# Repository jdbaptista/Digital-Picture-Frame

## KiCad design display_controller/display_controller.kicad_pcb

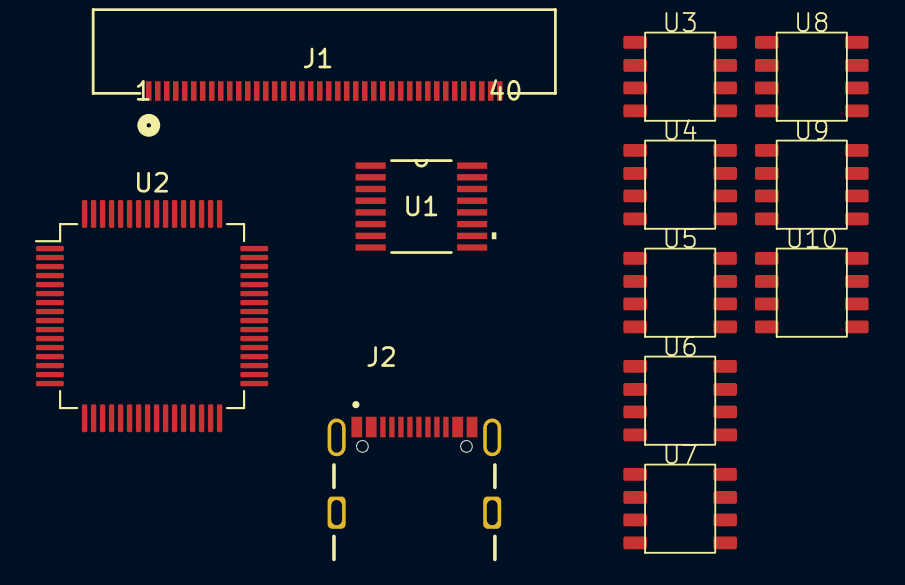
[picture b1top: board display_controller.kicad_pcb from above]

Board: 2 copper layers, 12 parts (0 on the bottom side), 10 nets, no tracks yet.

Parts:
J1: FPC CONN; CONN_4-1734592-0_TYCO
J2: USB4105GFA120; GCT_USB4105GFA120
U1: LVDS391; PW16
U2: STM32F412RETx; LQFP-64_10x10mm_P0.5mm
U3, U4, U5, U6, U7, U8, U9, U10: GD25Q16; SOP8 150mil

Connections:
GND: J1.7 (GND), J1.10 (GND), J1.13 (GND), J1.16 (GND), J1.19 (GND), J1.20 (RXIN3-), J1.21 (RXIN3+), J1.22 (GND), J1.23 (NC), J1.24 (NC), J1.25 (GND), J1.30 (GND), J1.36 (CABCEN1), J1.37 (CABCEN0)
unnamed: J1.18 (RXCLKIN+), U1.9 (4Z)
unnamed: J1.17 (RXCLKIN-), U1.10 (4Y)
unnamed: J1.9 (RXIN0+), U1.15 (1Z)
unnamed: J1.8 (RXIN0-), U1.16 (1Y)
unnamed: J1.12 (RXIN1+), U1.13 (2Z)
unnamed: J1.11 (RXIN1-), U1.14 (2Y)
unnamed: J1.15 (RXIN2+), U1.11 (3Z)
unnamed: J1.14 (RXIN2-), U1.12 (3Y)
unnamed: U2.18 (VSS), U2.31 (VSS), U2.47 (VSS), U2.63 (VSS)

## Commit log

2024-01-06 create kicad project
2024-01-06 update footprints
2024-01-07 change FPC connector
2024-01-11 Add flash modules, MCU, and usb-c receptacle
